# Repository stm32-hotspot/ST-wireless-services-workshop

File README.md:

# ST-wireless-services-workshop
Throughout the https://content.st.com/stm32-wireless-design-service-workshop.html session, you explored ST’s comprehensive hardware, RF, and software services, using the STM32WBA55, its Nucleo development board, and the STM32Cube ecosystem. 

You learned, through a virtual 2.4 GHz customer project, how ST design services can support your initial bring‑up activities.

You will find in this repository all the material used during the session and the associated collateral to replicate the activities on your own.

# The material used during session
- the PDF slides used during workshop session are available on main repository
- the FW based on STM32CubeWBA 1.9.0 used to generate Health Thermomterrunning over NUCLEO-WBA55CG [FW ressources](https://github.com/stm32-hotspot/ST-wireless-services-workshop/tree/main/WBA55_TH_sensor_FW)
- the schematics and layout files associated to Health Thermometer end customer PCB [HW ressources](https://github.com/stm32-hotspot/ST-wireless-services-workshop/tree/main/WBA55_TH_sensor_HW)

# how to replicate
To replicate the proof of concept (Health Thermometer  demonstrated in the first part of the workshop) you will need  
- [NUCLEO-WBA55CG](https://www.st.com/en/evaluation-tools/nucleo-wba55cg.html)
- [X-NUCLEO-IKS4A1](https://www.st.com/en/evaluation-tools/x-nucleo-iks4a1.html)
- [STM32CubeIDE](https://www.st.com/en/development-tools/stm32cubeide.html)
- The FW used to generate this application,[FW](https://github.com/stm32-hotspot/ST-wireless-services-workshop/tree/main/WBA55_TH_sensor_FW)
- [STBLEToolbox](https://www.st.com/en/embedded-software/stbletoolbox.html) App installed on your mobile
  
This application is based on BLE_HealthThermometer application from STM32CubeWBA 1.9.0. For more details you can refer to STM32CubeWBA 1.9.0 BLE_HealthThermometer readme.txt

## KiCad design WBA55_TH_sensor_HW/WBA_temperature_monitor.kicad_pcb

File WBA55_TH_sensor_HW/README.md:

# WBA55_TH_sensor – Hardware (KiCad)

This folder contains the **hardware design** for the WBA55_TH_sensor board:

- 4‑layer PCB
- Tuned 2.4 GHz antenna for STM32WBA55 wireless operation
- Designed in **KiCad 9.0.0**
- Based on **STM32WBA55** MCU and **SHT40AD1B** temperature/humidity sensor
- Powered from **CR2032** coin cell or external supply (see schematic)

The design can be used as a reference for integrating STM32WBA55 in low‑power BLE sensor applications.

## Contents

- KiCad project:
  - `*.kicad_pro`
  - `*.kicad_sch` (schematic)
  - `*.kicad_pcb` (PCB layout)
- Generated documentation:
  - Schematic and layout PDFs
  - Gerber files
  - BOM and component placement files

## How to use

1. Open the project in **KiCad 9.0.0**.
2. Review the schematic and 4‑layer stack‑up, including the tuned RF antenna section.
3. Adjust design parameters (components, layout, stack‑up) if needed for your application or PCB manufacturer.
4. Generate manufacturing outputs (Gerbers, drill, pick‑and‑place) from KiCad for board fabrication.

## Licensing

The hardware design files are provided under the terms described in the repository `LICENSE` file.

Third‑party components and trademarks (including but not limited to STM32WBA55 and SHT40AD1B) remain the property of their respective owners.

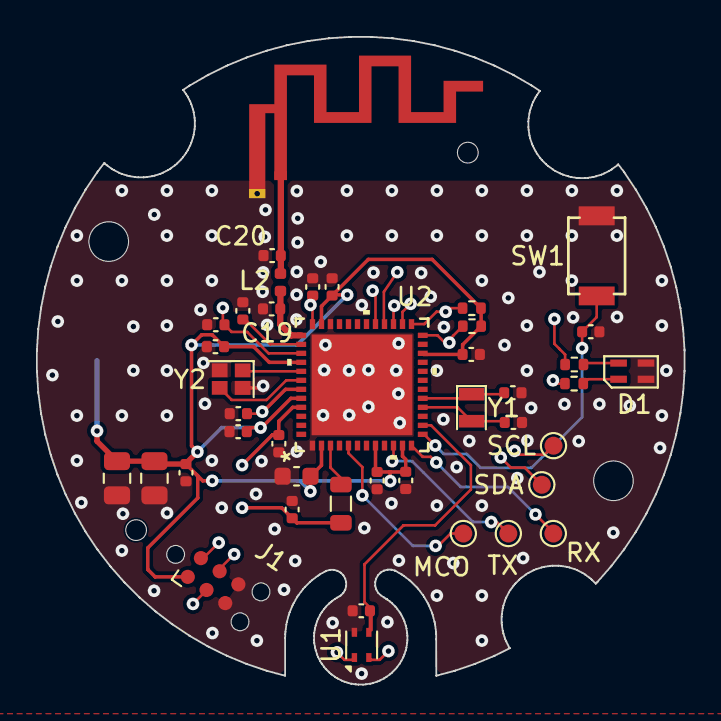
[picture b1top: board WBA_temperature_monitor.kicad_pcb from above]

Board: 4 copper layers, 36.0 x 36.0 mm, 46 parts (1 on the bottom side), 25 nets.

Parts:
AE1: Antenna_Shield; 2.4GHz_centered
BT1: Battery_Cell; BatteryHolder_Keystone_1060_1x2032
C1, C2, C3, C4, C6, C7, C9, C12, C13, C14, C15: 100n; C_0402_1005Metric
C5: 47u; C_0805_2012Metric
C8: 10u; C_0805_2012Metric
C10: 10u; C_0402_1005Metric
C11: 470n; C_0402_1005Metric
C16: 10n; C_0402_1005Metric
C17: 4.7 uF; C_0402_1005Metric
C18: 10u; C_0603_1608Metric
C19, C20: 1p2; C_0402_1005Metric
C21, C22: 6p; C_0402_1005Metric
D1: LED_Dual_AKAK; SML-522MUWT86_4P_RG_LED
H1, H2: MountingHole; MountingHole_2.2mm_M2
H3, H4: Tooling Hole; ToolingHole_1.152mm
J1: Conn_ARM_SWD_TagConnect_TC2030-NL; Tag-Connect_TC2030-IDC-NL_2x03_P1.27mm_Vertical
L1: 2.2 uH; L_0805_2012Metric
L2: 3n3; L_0402_1005Metric
MCO: TestPoint; TestPoint_Pad_D1.0mm
R1, R2: 10k; R_0402_1005Metric
R3, R4: 1k; R_0402_1005Metric
RX: TestPoint; TestPoint_Pad_D1.0mm
SCL: TestPoint; TestPoint_Pad_D1.0mm
SDA: TestPoint; TestPoint_Pad_D1.0mm
SW1: SW_Push; TS-1088-AR02016
TX: TestPoint; TestPoint_Pad_D1.0mm
U1: SHT4x; Sensirion_DFN-4_1.5x1.5mm_P0.8mm_SHT4x_NoCentralPad
U2: STM32WBA55CGUx; UFQFPN-48_STM
Y1: Crystal; Crystal_SMD_2012-2Pin_TF2012
Y2: Crystal_GND24; Crystal_SMD_2016-4Pin_2.0x1.6mm_abracon

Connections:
/RFpath2: AE1.1 (A), C20.1, L2.2
BUTTON_INT: C16.1, SW1.2, U2.13 (PA0)
GND: AE1.2 (Shield), BT1.2 (-), C1.2, C2.2, C3.2, C4.2, C5.2, C6.2, C7.1, C8.2, C9.2, C10.2, C11.2, C12.2, C13.2, C14.1, C15.1, C16.2, C17.2, C18.2, C19.2, C20.2, C21.2, C22.2, D1.2 (K1), D1.4 (K2), J1.5 (GND), J1.6 (SWO), SW1.1, U1.4 (VSS), U2.1 (VSSSMPS), U2.34 (PH3), U2.49 (VSS), Y2.2, Y2.4
I2C_SCL: R2.1, SCL.1, U1.2 (SCL), U2.25 (PA15)
I2C_SDA: R1.1, SDA.1, U1.1 (SDA), U2.24 (PB3)
LED_GREEN: R3.2, U2.28 (PA12)
LED_RED: R4.2, U2.29 (PA11)
NRST: C1.1, J1.3 (~RESET), U2.36 (NRST)
unnamed: D1.1 (A1), R4.1
unnamed: D1.3 (A2), R3.1
unnamed: L1.2, U2.3 (VLXSMPS)
OSC32_IN: C21.1, U2.17 (PC14), Y1.1
OSC32_OUT: C22.1, U2.16 (PC15), Y1.2
OSC_IN: U2.42 (OSC_IN), Y2.3
OSC_OUT: U2.41 (OSC_OUT), Y2.1
RCC_MCO: MCO.1, U2.5 (PA8)
RF: C19.1, L2.1, U2.37 (RF)
SHT40_VDD: C13.1, U1.3 (VDD), U2.14 (PB9)
SMPS_OUT: C7.2, C14.2, C15.2, C17.1, L1.1, U2.39 (VDDANA), U2.43 (VDDRFPA), U2.45 (VDD11)
SWCLK: J1.4 (SWCLK), U2.26 (PA14)
SWDIO: J1.2 (SWDIO), U2.27 (PA13)
UART_RX: RX.1, U2.12 (PA1)
UART_TX: TX.1, U2.10 (PA2)
VDD: BT1.1 (+), C2.1, C3.1, C4.1, C5.1, C6.1, C8.1, C9.1, C10.1, C12.1, C18.1, J1.1 (VCC), R1.2, R2.2, U2.2 (VDDSMPS), U2.8 (VDDA), U2.11 (VDD), U2.22 (VDD), U2.35 (VDD), U2.40 (VDDRF), U2.44 (VDD)
VDDHPA: C11.1, U2.38 (VDDHPA)

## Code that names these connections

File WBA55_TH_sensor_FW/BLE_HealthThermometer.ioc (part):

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Mcu.Name=STM32WBA55CGUx
Mcu.Package=UFQFPN48
Mcu.UserName=STM32WBA55CGUx
PA13\ (JTMS/SWDIO).Mode=Serial_Wire
PA13\ (JTMS/SWDIO).Signal=DEBUG_JTMS-SWDIO
PA14\ (JTCK/SWCLK).Mode=Serial_Wire
PA14\ (JTCK/SWCLK).Signal=DEBUG_JTCK-SWCLK
PA8.Mode=Asynchronous
PA8.Signal=USART1_RX
PB1.Mode=I2C
PB1.Signal=I2C1_SDA
PB12.Mode=Asynchronous
PB12.Signal=USART1_TX
PB2.Mode=I2C
PB2.Signal=I2C1_SCL
PC14-OSC32_IN.Mode=LSE-External-Oscillator
PC14-OSC32_IN.Signal=RCC_OSC32_IN
PC15-OSC32_OUT.Mode=LSE-External-Oscillator
PC15-OSC32_OUT.Signal=RCC_OSC32_OUT
RCC.HSESYSFreq_VALUE=32000000
RCC.HSE_VALUE=32000000
RCC.SYSCLKFreq_VALUE=32000000
RCC.SYSCLKSourceVirtual=RCC_SYSCLKSOURCE_HSE
board=custom

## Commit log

2026-03-23 content upload
2026-03-24 Create add materials
